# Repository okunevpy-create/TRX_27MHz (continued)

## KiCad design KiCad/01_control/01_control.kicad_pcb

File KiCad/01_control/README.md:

# 01_control — плата управления (этап 1)

## Подэтапы
- **1.1** — Входной узел защиты (без F1, питание от LTC3780 13,8 В) + DC-DC 12→5 В (LM2596S-5.0) + LDO 3,3 В + `+3V3_SI`
- **1.2** — MCU: STM32F411 + кварц + SWD + UART + EEPROM (AT24C02C, I²C)
- **1.3** — Синтезатор: Si5351 + буферы VFO/BFO
- **1.4** — UI: OLED + энкодер + память каналов + RIT + squelch (программный); пады под проводной монтаж: MIC (с корпусного разъёма 2.5 мм), PTT (с корпусного разъёма 2.5 мм), GND; цепь питания электрета (резистор 2–10 кОм от +3.3 В), микрофонный предусилитель, выход `MIC_LINE`
- **1.5** — Интерфейсы и логика: PTT, входы I_sense/SWR_sense/PWR_LIMIT_SW/RX_audio, выход PWR_LIMIT_EN, разъёмы; вход `PTT` с гарнитуры (чтение MCU), выход `MUTE` на `03_rx_tx`

## Ключевые компоненты
- STM32F411CEU6 (LQFP-48), кварц 8 МГц, SWD, UART, USB DFU.
- EEPROM AT24C02C (SOIC-8/SOP-8, I²C 0x50) — хранение RIT/каналов (U10 + C45 100 нФ).
- Si5351A-B-GT (MSOP-10) + посадочное место под модуль.
- LM2596S-5.0 (TO-263) → LDO 3,3 В; отдельный LDO `+3V3_SI`.
- Входной узел: только `J_12V_IN_1` (клеммник 2-pin); входная защита (предохранитель 5 А + TVS load dump + диод реверса SS54) — на корпусе перед предрегулятором LTC3780 13,8 В / 7 А. D1/D2 (TVS SMBJ18A + SS34) сняты с платы.
- ≤ 9×9 см, 2 слоя, VIA — клёпки 0.9 мм.

## Разъёмы
- J_PA_CTRL — см. `docs/contracts/control_pa.md`
- J_RXTX_SIG — см. `docs/contracts/control_rxtx.md`
- Питание: вход `J_12V_IN_1`; раздача +12V на УМ/RX-TX — через внешние WAGO 221-415 (не через плату).
- OLED, энкодер, SWD, UART, USB.

## ⚠️ Порядок работ и запрет на изготовление
1. Зафиксировать `control_pa.md` и `control_rxtx.md`.
2. Схемотехника 1.1–1.4.
3. Схемотехника этапа 2, подэтапы 2.1–2.2.
4. **Совместно** 1.5 + 2.3.
5. **Только после этого** — травление и монтаж платы этапа 1.

До шага 5 разрешена только схемотехника и разводка в KiCad, без травления.

## Статус
Схема построена (подэтапы 1.1–1.6), **ERC = 0 ошибок** (7 warning `footprint_link_issues` — исключены). Предохранитель F1 снят с платы (защита входа — на корпусе перед LTC3780 13,8 В / 7 А). Добавлен **EEPROM AT24C02C (U10)** на шину I²C (PB6/PB7) — RIT/каналы.

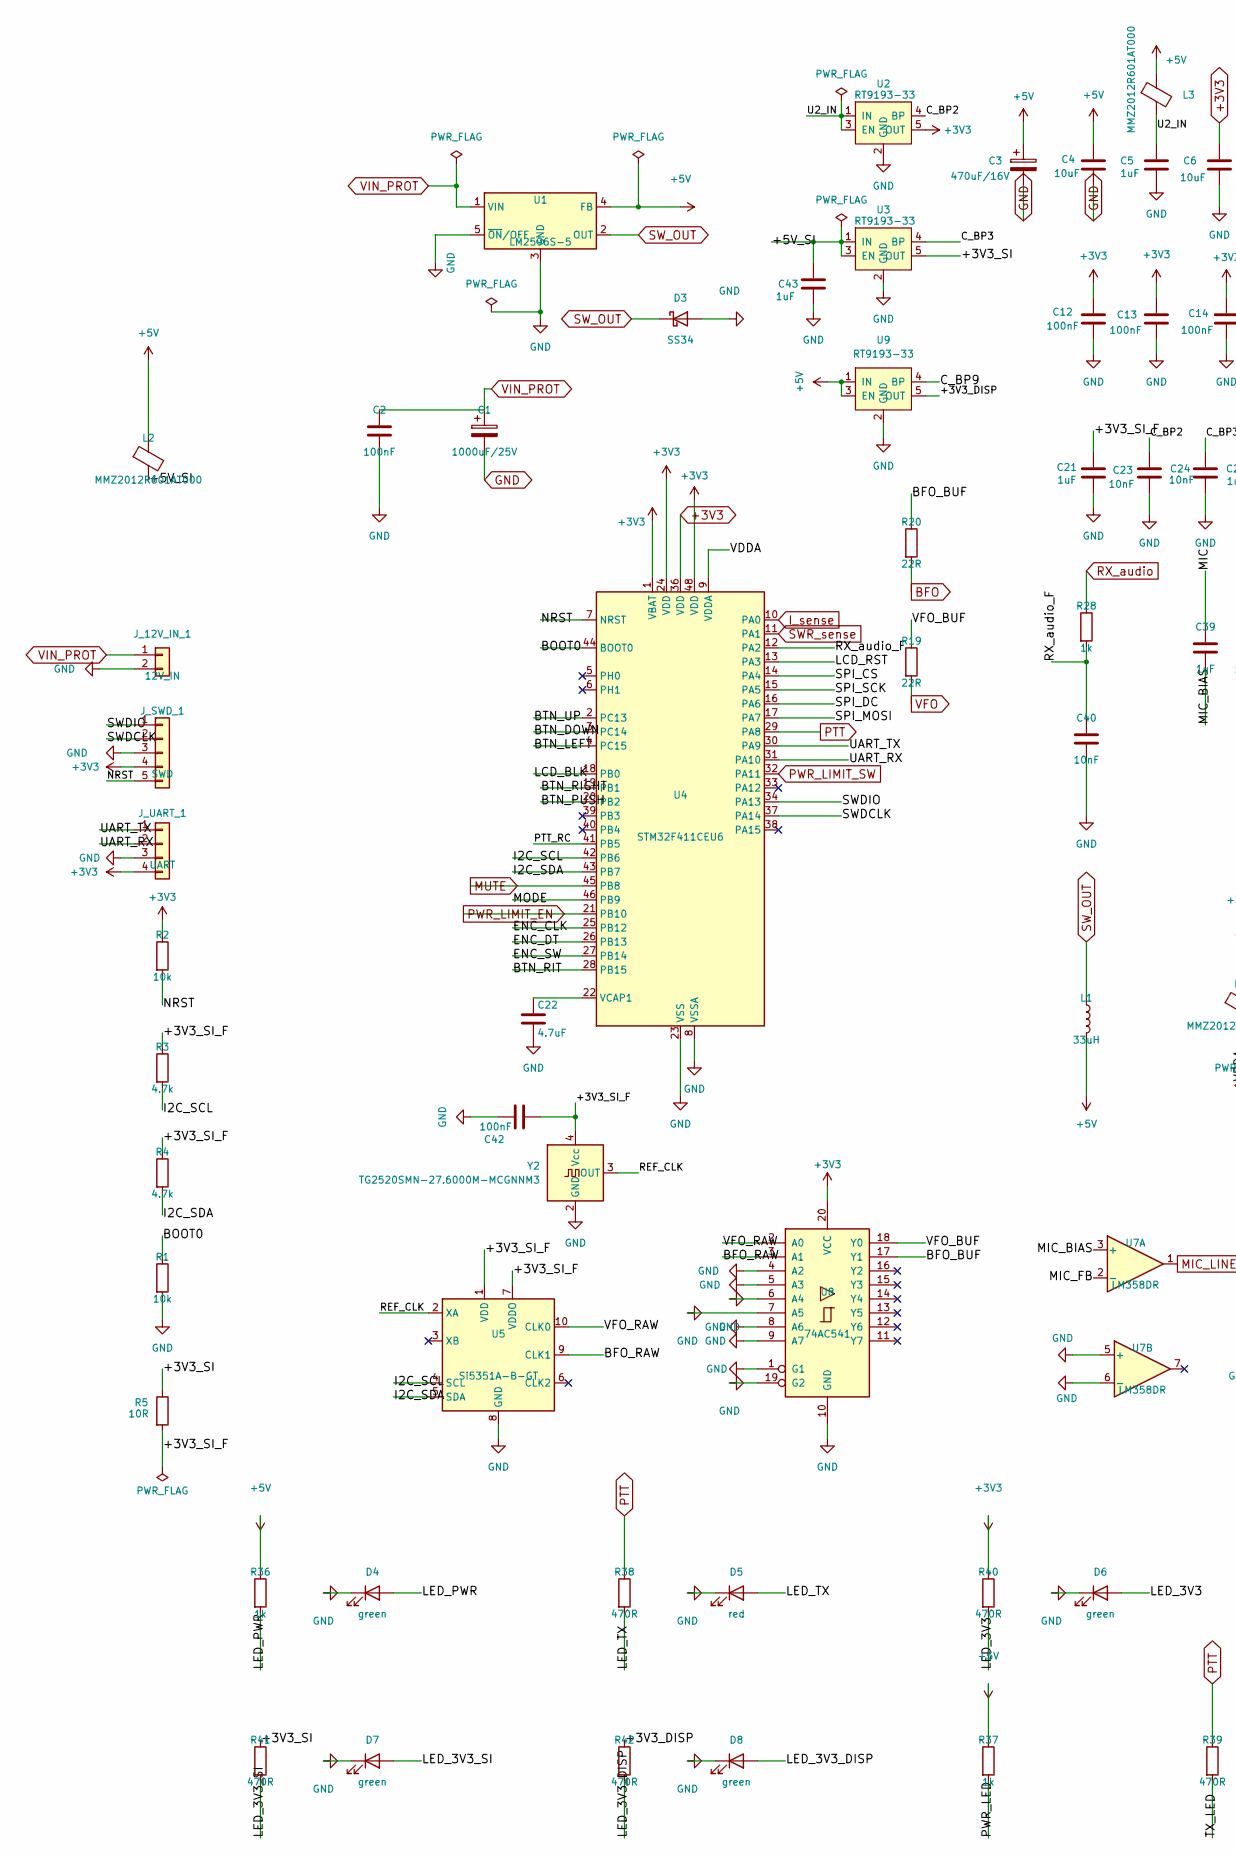
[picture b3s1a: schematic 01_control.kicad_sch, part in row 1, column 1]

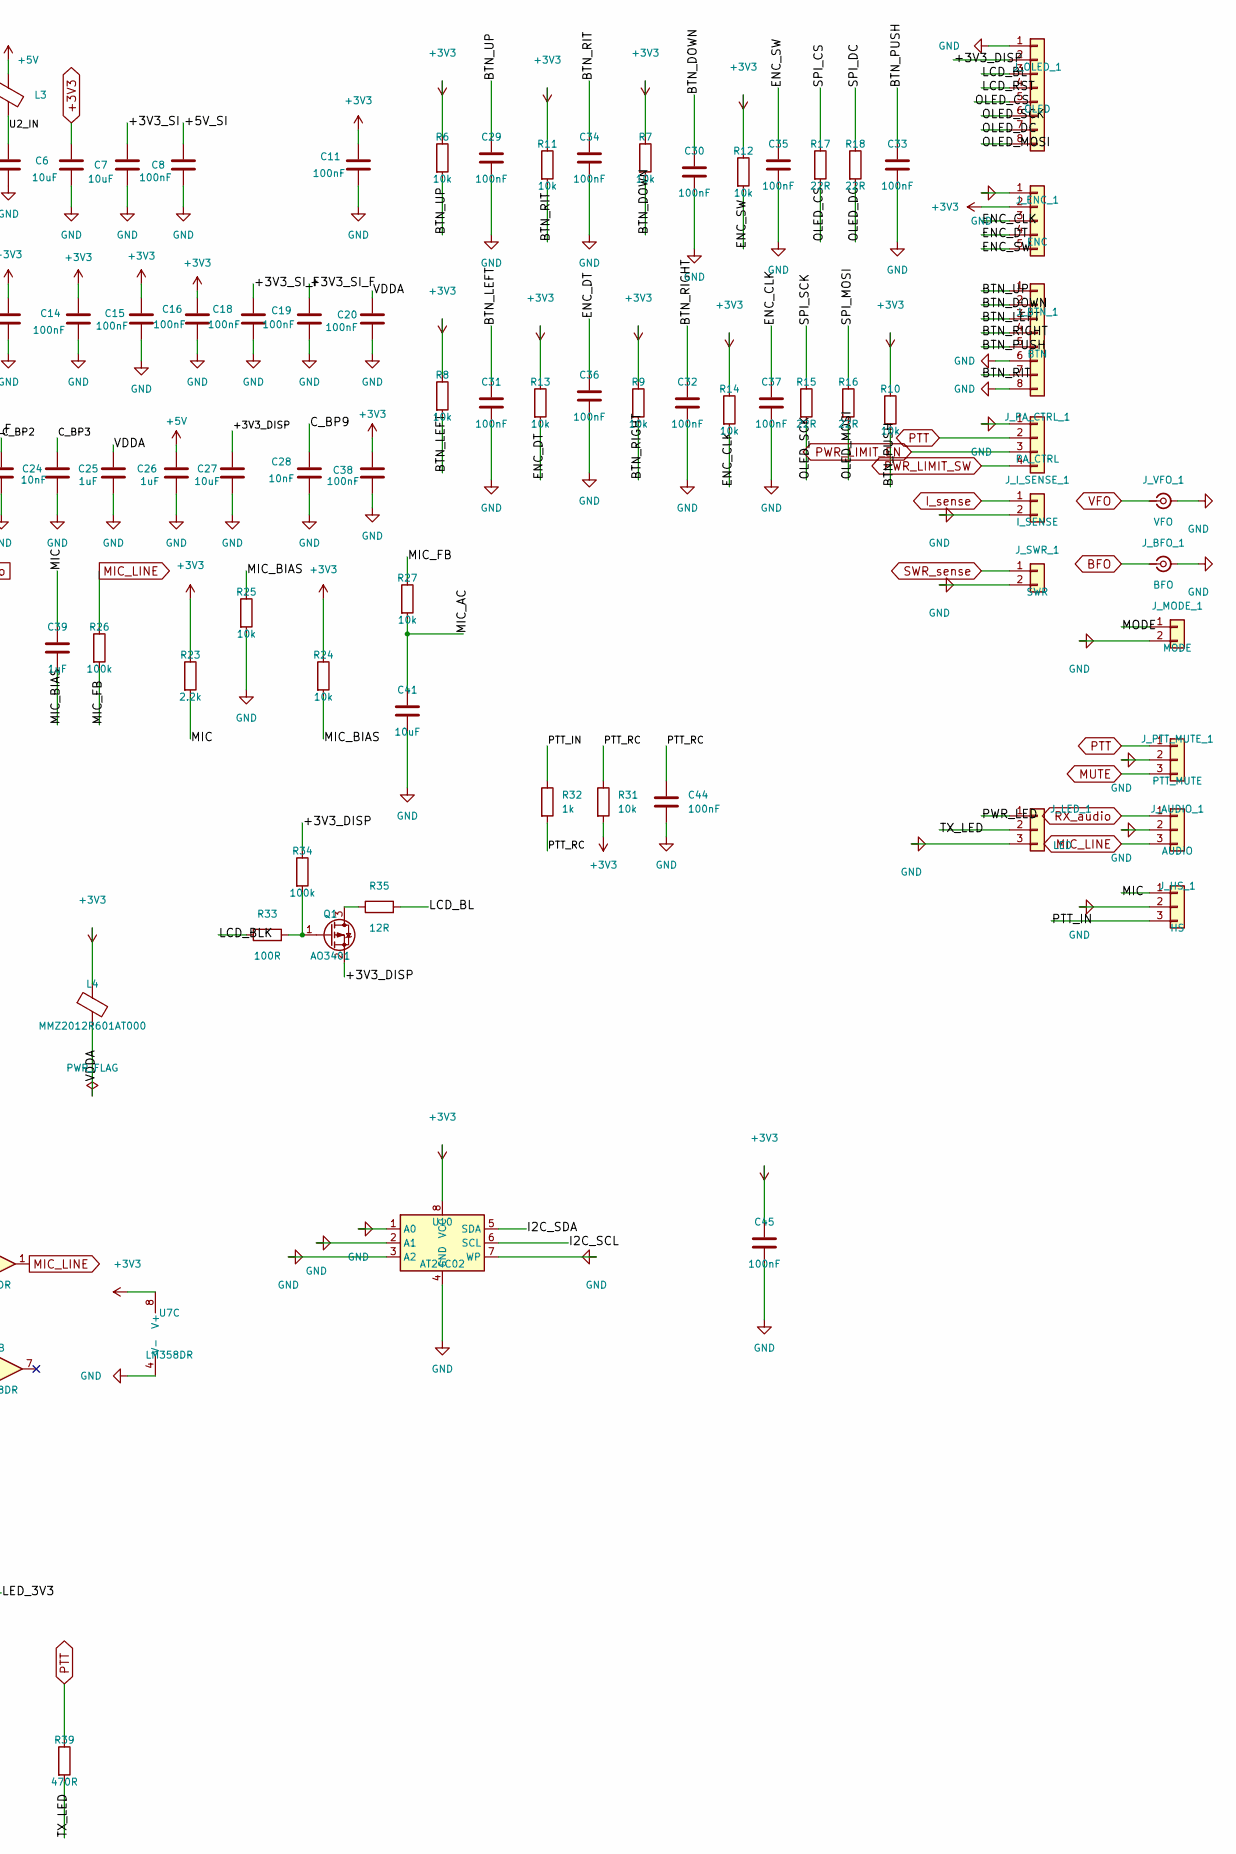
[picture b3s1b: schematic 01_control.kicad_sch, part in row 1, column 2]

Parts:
C1: 1000uF/25V; CP_Elec_10x12.5
C2, C8, C11, C12, C13, C14, C15, C16, C18, C19, C20, C29, C30, C31, C32, C33, C34, C35, C36, C37, C38, C42, C44, C45: 100nF; C_0603_1608Metric_Pad1.08x0.95mm_HandSolder
C3: 470uF/16V; CP_Elec_8x10.5
C4, C6, C7, C27, C41: 10uF; C_0805_2012Metric_Pad1.18x1.45mm_HandSolder
C5, C21, C25, C26, C39, C43: 1uF; C_0603_1608Metric_Pad1.08x0.95mm_HandSolder
C22: 4.7uF; C_0603_1608Metric_Pad1.08x0.95mm_HandSolder
C23, C24, C28, C40: 10nF; C_0603_1608Metric_Pad1.08x0.95mm_HandSolder
D3: SS34; D_SMA_Handsoldering
D4, D6, D7, D8: green; LED_0805_2012Metric_Pad1.15x1.40mm_HandSolder
D5: red; LED_0805_2012Metric_Pad1.15x1.40mm_HandSolder
J_12V_IN_1: 12V_IN; TerminalBlock_Phoenix_MKDS-1,5-2_1x02_P5.00mm_Horizontal
J_AUDIO_1: AUDIO; JST_XH_B3B-XH-A_1x03_P2.50mm_Vertical
J_BFO_1: BFO; SMA_S-P215
J_BTN_1: BTN; JST_XH_B8B-XH-A_1x08_P2.50mm_Vertical
J_ENC_1: ENC; JST_XH_B5B-XH-A_1x05_P2.50mm_Vertical
J_HS_1: HS; JST_XH_B3B-XH-A_1x03_P2.50mm_Vertical
J_I_SENSE_1: I_SENSE; JST_XH_B2B-XH-A_1x02_P2.50mm_Vertical
J_LED_1: LED; JST_XH_B3B-XH-A_1x03_P2.50mm_Vertical
J_MODE_1: MODE; JST_XH_B2B-XH-A_1x02_P2.50mm_Vertical
J_OLED_1: OLED; JST_XH_B8B-XH-A_1x08_P2.50mm_Vertical
J_PA_CTRL_1: PA_CTRL; JST_XH_B4B-XH-A_1x04_P2.50mm_Vertical
J_PTT_MUTE_1: PTT_MUTE; JST_XH_B3B-XH-A_1x03_P2.50mm_Vertical
J_SWD_1: SWD; PinHeader_1x05_P2.54mm_Vertical
J_SWR_1: SWR; JST_XH_B2B-XH-A_1x02_P2.50mm_Vertical
J_UART_1: UART; PinHeader_1x04_P2.54mm_Vertical
J_VFO_1: VFO; SMA_S-P215
L1: 33uH; L_12x12mm_H4.5mm
L2, L3, L4: MMZ2012R601AT000; L_0805_2012Metric
Q1: AO3401; SOT-23_Handsoldering
R1, R2, R6, R7, R8, R9, R10, R11, R12, R13, R14, R24, R25, R27, R31: 10k; R_0603_1608Metric_Pad0.98x0.95mm_HandSolder
R3, R4: 4.7k; R_0603_1608Metric_Pad0.98x0.95mm_HandSolder
R5: 10R; R_0603_1608Metric_Pad0.98x0.95mm_HandSolder
R15, R16, R17, R18, R19, R20: 22R; R_0603_1608Metric_Pad0.98x0.95mm_HandSolder
R23: 2.2k; R_0603_1608Metric_Pad0.98x0.95mm_HandSolder
R26, R34: 100k; R_0603_1608Metric_Pad0.98x0.95mm_HandSolder
R28, R32, R36, R37: 1k; R_0603_1608Metric_Pad0.98x0.95mm_HandSolder
R33: 100R; R_0603_1608Metric_Pad0.98x0.95mm_HandSolder
R35: 12R; R_1210_3225Metric_Pad1.30x2.65mm_HandSolder
R38, R39, R40, R41, R42: 470R; R_0603_1608Metric_Pad0.98x0.95mm_HandSolder
U1: LM2596S-5; TO-263-5_TabPin3
U2, U3, U9: RT9193-33; SOT-23-5
U4: STM32F411CEU6; QFN-48-1EP_7x7mm_P0.5mm_EP5.6x5.6mm
U5: Si5351A-B-GT; MSOP-10_3x3mm_P0.5mm
U7: LM358DR; SOIC-8_3.9x4.9mm_P1.27mm
U8: 74AC541; SOIC-20W_7.5x12.8mm_P1.27mm
U10: AT24C02; SOIC-8_3.9x4.9mm_P1.27mm
Y2: TG2520SMN-27.6000M-MCGNNM3; Oscillator_SMD_SeikoEpson_TG2520SMN-xxx-xxxxxx-4Pin_2.5x2.0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

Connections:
+3V3: C6.1, C11.1, C12.1, C13.1, C14.1, C15.1, C16.1, C38.1, C45.1, J_ENC_1.2, J_SWD_1.4, J_UART_1.4, L4.1, R2.1, R6.1, R7.1, R8.1, R9.1, R10.1, R11.1, R12.1, R13.1, R14.1, R23.1, R24.1, R31.2, R40.1, U2.5 (OUT), U4.1 (VBAT), U4.24 (VDD), U4.36 (VDD), U4.48 (VDD), U7.8 (V+), U8.20 (VCC), U10.8 (VCC)
+5V: C3.1, C4.1, C26.1, L1.2, L2.1, L3.1, R36.1, R37.1, U1.4 (FB), U9.1 (IN), U9.3 (EN)
/+3V3_DISP: C27.1, J_OLED_1.2, Q1.2 (S), R34.1, R42.1, U9.5 (OUT)
/+3V3_SI: C7.1, R5.1, R41.1, U3.5 (OUT)
/+5V_SI: C8.1, C43.1, L2.2, U3.1 (IN), U3.3 (EN)
/BFO_BUF: R20.1, U8.17 (Y1)
/BFO_RAW: U5.9 (CLK1), U8.3 (A1)
/BOOT0: R1.1, U4.44 (BOOT0)
/BTN_DOWN: C30.1, J_BTN_1.2, R7.2, U4.3 (PC14)
/BTN_LEFT: C31.1, J_BTN_1.3, R8.2, U4.4 (PC15)
/BTN_PUSH: C33.1, J_BTN_1.5, R10.2, U4.20 (PB2)
/BTN_RIGHT: C32.1, J_BTN_1.4, R9.2, U4.19 (PB1)
/BTN_RIT: C34.1, J_BTN_1.7, R11.2, U4.28 (PB15)
/BTN_UP: C29.1, J_BTN_1.1, R6.2, U4.2 (PC13)
/C_BP2: C23.1, U2.4 (BP)
/C_BP3: C24.1, U3.4 (BP)
/C_BP9: C28.1, U9.4 (BP)
/ENC_CLK: C37.1, J_ENC_1.3, R14.2, U4.25 (PB12)
/ENC_DT: C36.1, J_ENC_1.4, R13.2, U4.26 (PB13)
/ENC_SW: C35.1, J_ENC_1.5, R12.2, U4.27 (PB14)
/I2C_SCL: R3.2, U4.42 (PB6), U5.4 (SCL), U10.6 (SCL)
/I2C_SDA: R4.2, U4.43 (PB7), U5.5 (SDA), U10.5 (SDA)
/LCD_BL: J_OLED_1.3, R35.2
/LCD_BLK: R33.1, U4.18 (PB0)
/LCD_RST: J_OLED_1.4, U4.13 (PA3)
/LED_3V3: D6.2 (A), R40.2
/LED_3V3_DISP: D8.2 (A), R42.2
/LED_3V3_SI: D7.2 (A), R41.2
/LED_PWR: D4.2 (A), R36.2
/LED_TX: D5.2 (A), R38.2
/MIC: C39.1, J_HS_1.1, R23.2
/MIC_AC: C41.1, R27.2
/MIC_BIAS: C39.2, R24.2, R25.1, U7.3 (+)
/MIC_FB: R26.2, R27.1, U7.2 (-)
/MODE: J_MODE_1.1, U4.46 (PB9)
/NRST: J_SWD_1.5, R2.2, U4.7 (NRST)
/OLED_CS: J_OLED_1.5, R17.2
/OLED_DC: J_OLED_1.7, R18.2
/OLED_MOSI: J_OLED_1.8, R16.2
/OLED_SCK: J_OLED_1.6, R15.2
/PTT_IN: J_HS_1.3, R32.1
/PTT_RC: C44.1, R31.1, R32.2, U4.41 (PB5)
/PWR_LED: J_LED_1.1, R37.2
/REF_CLK: U5.2 (XA), Y2.3 (OUT)
/RX_audio_F: C40.1, R28.2, U4.12 (PA2)
/SPI_CS: R17.1, U4.14 (PA4)
/SPI_DC: R18.1, U4.16 (PA6)
/SPI_MOSI: R16.1, U4.17 (PA7)
/SPI_SCK: R15.1, U4.15 (PA5)
/SWDCLK: J_SWD_1.2, U4.37 (PA14)
/SWDIO: J_SWD_1.1, U4.34 (PA13)
/TX_LED: J_LED_1.2, R39.2
/UART_RX: J_UART_1.2, U4.31 (PA10)
/UART_TX: J_UART_1.1, U4.30 (PA9)
/VFO_BUF: R19.1, U8.18 (Y0)
/VFO_RAW: U5.10 (CLK0), U8.2 (A0)
BFO: J_BFO_1.1 (In), R20.2
GND: C1.2, C2.2, C3.2, C4.2, C5.2, C6.2, C7.2, C8.2, C11.2, C12.2, C13.2, C14.2, C15.2, C16.2, C18.2, C19.2, C20.2, C21.2, C22.2, C23.2, C24.2, C25.2, C26.2, C27.2, C28.2, C29.2, C30.2, C31.2, C32.2, C33.2, C34.2, C35.2, C36.2, C37.2, C38.2, C40.2, C41.2, C42.2, C43.2, C44.2, C45.2, D3.2 (A), D4.1 (K), D5.1 (K), D6.1 (K), D7.1 (K), D8.1 (K), J_12V_IN_1.2, J_AUDIO_1.2, J_BFO_1.2 (Ext), J_BTN_1.6, J_BTN_1.8, J_ENC_1.1, J_HS_1.2, J_I_SENSE_1.2, J_LED_1.3, J_MODE_1.2, J_OLED_1.1, J_PA_CTRL_1.1, J_PTT_MUTE_1.2, J_SWD_1.3, J_SWR_1.2, J_UART_1.3, J_VFO_1.2 (Ext), R1.2, R25.2, U1.3 (GND), U1.5 (~ON/OFF), U2.2 (GND), U3.2 (GND), U4.8 (VSSA), U4.23 (VSS), U4.35 (VSS), U4.47 (VSS), U4.49 (VSS), U5.8 (GND), U7.4 (V-), U7.5 (+), U7.6 (-), U8.1 (G1), U8.4 (A2), U8.5 (A3), U8.6 (A4), U8.7 (A5), U8.8 (A6), U8.9 (A7), U8.10 (GND), U8.19 (G2), U9.2 (GND), U10.1 (A0), U10.2 (A1), U10.3 (A2), U10.4 (GND), U10.7 (WP), Y2.2 (GND)
I_sense: J_I_SENSE_1.1, U4.10 (PA0)
MIC_LINE: J_AUDIO_1.3, R26.1, U7.1
MUTE: J_PTT_MUTE_1.3, U4.45 (PB8)
unnamed: Q1.3 (D), R35.1
unnamed: Q1.1 (G), R33.2, R34.2
unnamed: C22.1, U4.22 (VCAP1)
PTT: J_PA_CTRL_1.2, J_PTT_MUTE_1.1, R38.1, R39.1, U4.29 (PA8)
PWR_LIMIT_EN: J_PA_CTRL_1.3, U4.21 (PB10)
PWR_LIMIT_SW: J_PA_CTRL_1.4, U4.32 (PA11)
RX_audio: J_AUDIO_1.1, R28.1
SWR_sense: J_SWR_1.1, U4.11 (PA1)
SW_OUT: D3.1 (K), L1.1, U1.2 (OUT)
VFO: J_VFO_1.1 (In), R19.2
VIN_PROT: C1.1, C2.1, J_12V_IN_1.1, U1.1 (VIN)

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
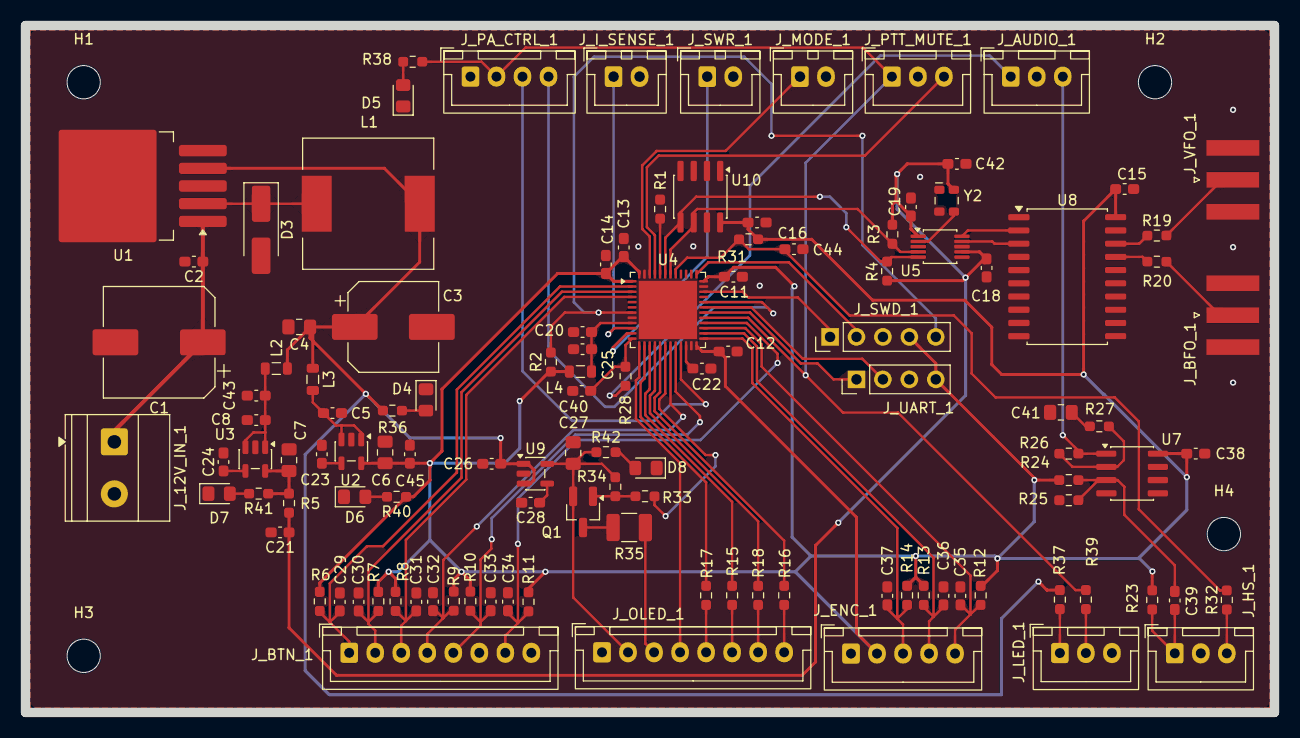
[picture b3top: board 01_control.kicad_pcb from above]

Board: 2 copper layers, 120.0 x 66.0 mm, 121 parts (0 on the bottom side), 75 nets.

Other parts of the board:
H1, H2, H3, H4: MountingHole_3.2mm_M3

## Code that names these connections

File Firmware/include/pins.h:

#pragma once
// TRX 27 MHz — плата управления (01_control)
// Единая точка истины для маппинга GPIO.
// Источник: docs/firmware_ui_ux.md §1 + docs/bom/stage1_control.md §1.5.
// Все кнопки/энкодер — активный низкий уровень (замыкание на GND, pull-up 10 кОм на плате).

#include <Arduino.h>

// ---- Дисплей ST7789 (SPI1 + программные CS/DC/RST, подсветка PWM) ----
#define PIN_LCD_SCK    PA5    // SPI1 SCK
#define PIN_LCD_MOSI   PA7    // SPI1 MOSI
#define PIN_LCD_CS     PA4    // SPI_CS  (GPIO)
#define PIN_LCD_DC     PA6    // SPI_DC  (GPIO)
#define PIN_LCD_RST    PA3    // LCD_RST (GPIO)
#define PIN_LCD_BL     PB0    // LCD_BLK (PWM, active-low ключ Q1)

// ---- Энкодер HW-040 (CLK/DT/SW) ----
#define PIN_ENC_CLK    PB12
#define PIN_ENC_DT     PB13
#define PIN_ENC_SW     PB14

// ---- Джойстик 5-поз. + кнопка RIT (J_BTN_1) ----
#define PIN_BTN_UP     PC13
#define PIN_BTN_DOWN   PC14
#define PIN_BTN_LEFT   PC15
#define PIN_BTN_RIGHT  PB1
#define PIN_BTN_PUSH   PB2
#define PIN_BTN_RIT    PB15

// ---- PTT ----
#define PIN_PTT_IN     PB5    // вход с гарнитуры (active-low: 0 = передача)
#define PIN_PTT_OUT    PA8    // выход на PA/RX-TX (0/3.3 В, 1 = TX)

// ---- Режим / squelch / ограничитель ----
#define PIN_MODE          PB9   // 0=SSB, 1=AM
#define PIN_MUTE          PB8   // 1=заглушить УНЧ
#define PIN_PWR_LIMIT_EN  PB10  // 1=включить ограничитель (единственный ключ Q3, вариант C)
#define PIN_PWR_LIMIT_SW  PA11  // вход: 1=LIMIT, 0=FULL

// ---- ADC ----
#define PIN_ADC_I_SENSE   PA0   // ток УМ
#define PIN_ADC_SWR       PA1   // КСВ
#define PIN_ADC_RX_AUDIO  PA2   // RX_audio (squelch)

// ---- I2C (Si5351 + EEPROM AT24C02C) ----
#define PIN_I2C_SCL     PB6
#define PIN_I2C_SDA     PB7
